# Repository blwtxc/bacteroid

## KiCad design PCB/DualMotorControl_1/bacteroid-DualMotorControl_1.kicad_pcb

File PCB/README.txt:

PCB design: 
KiCAD
http://www.kicad-pcb.org/display/KICAD/KiCad+EDA+Software+Suite

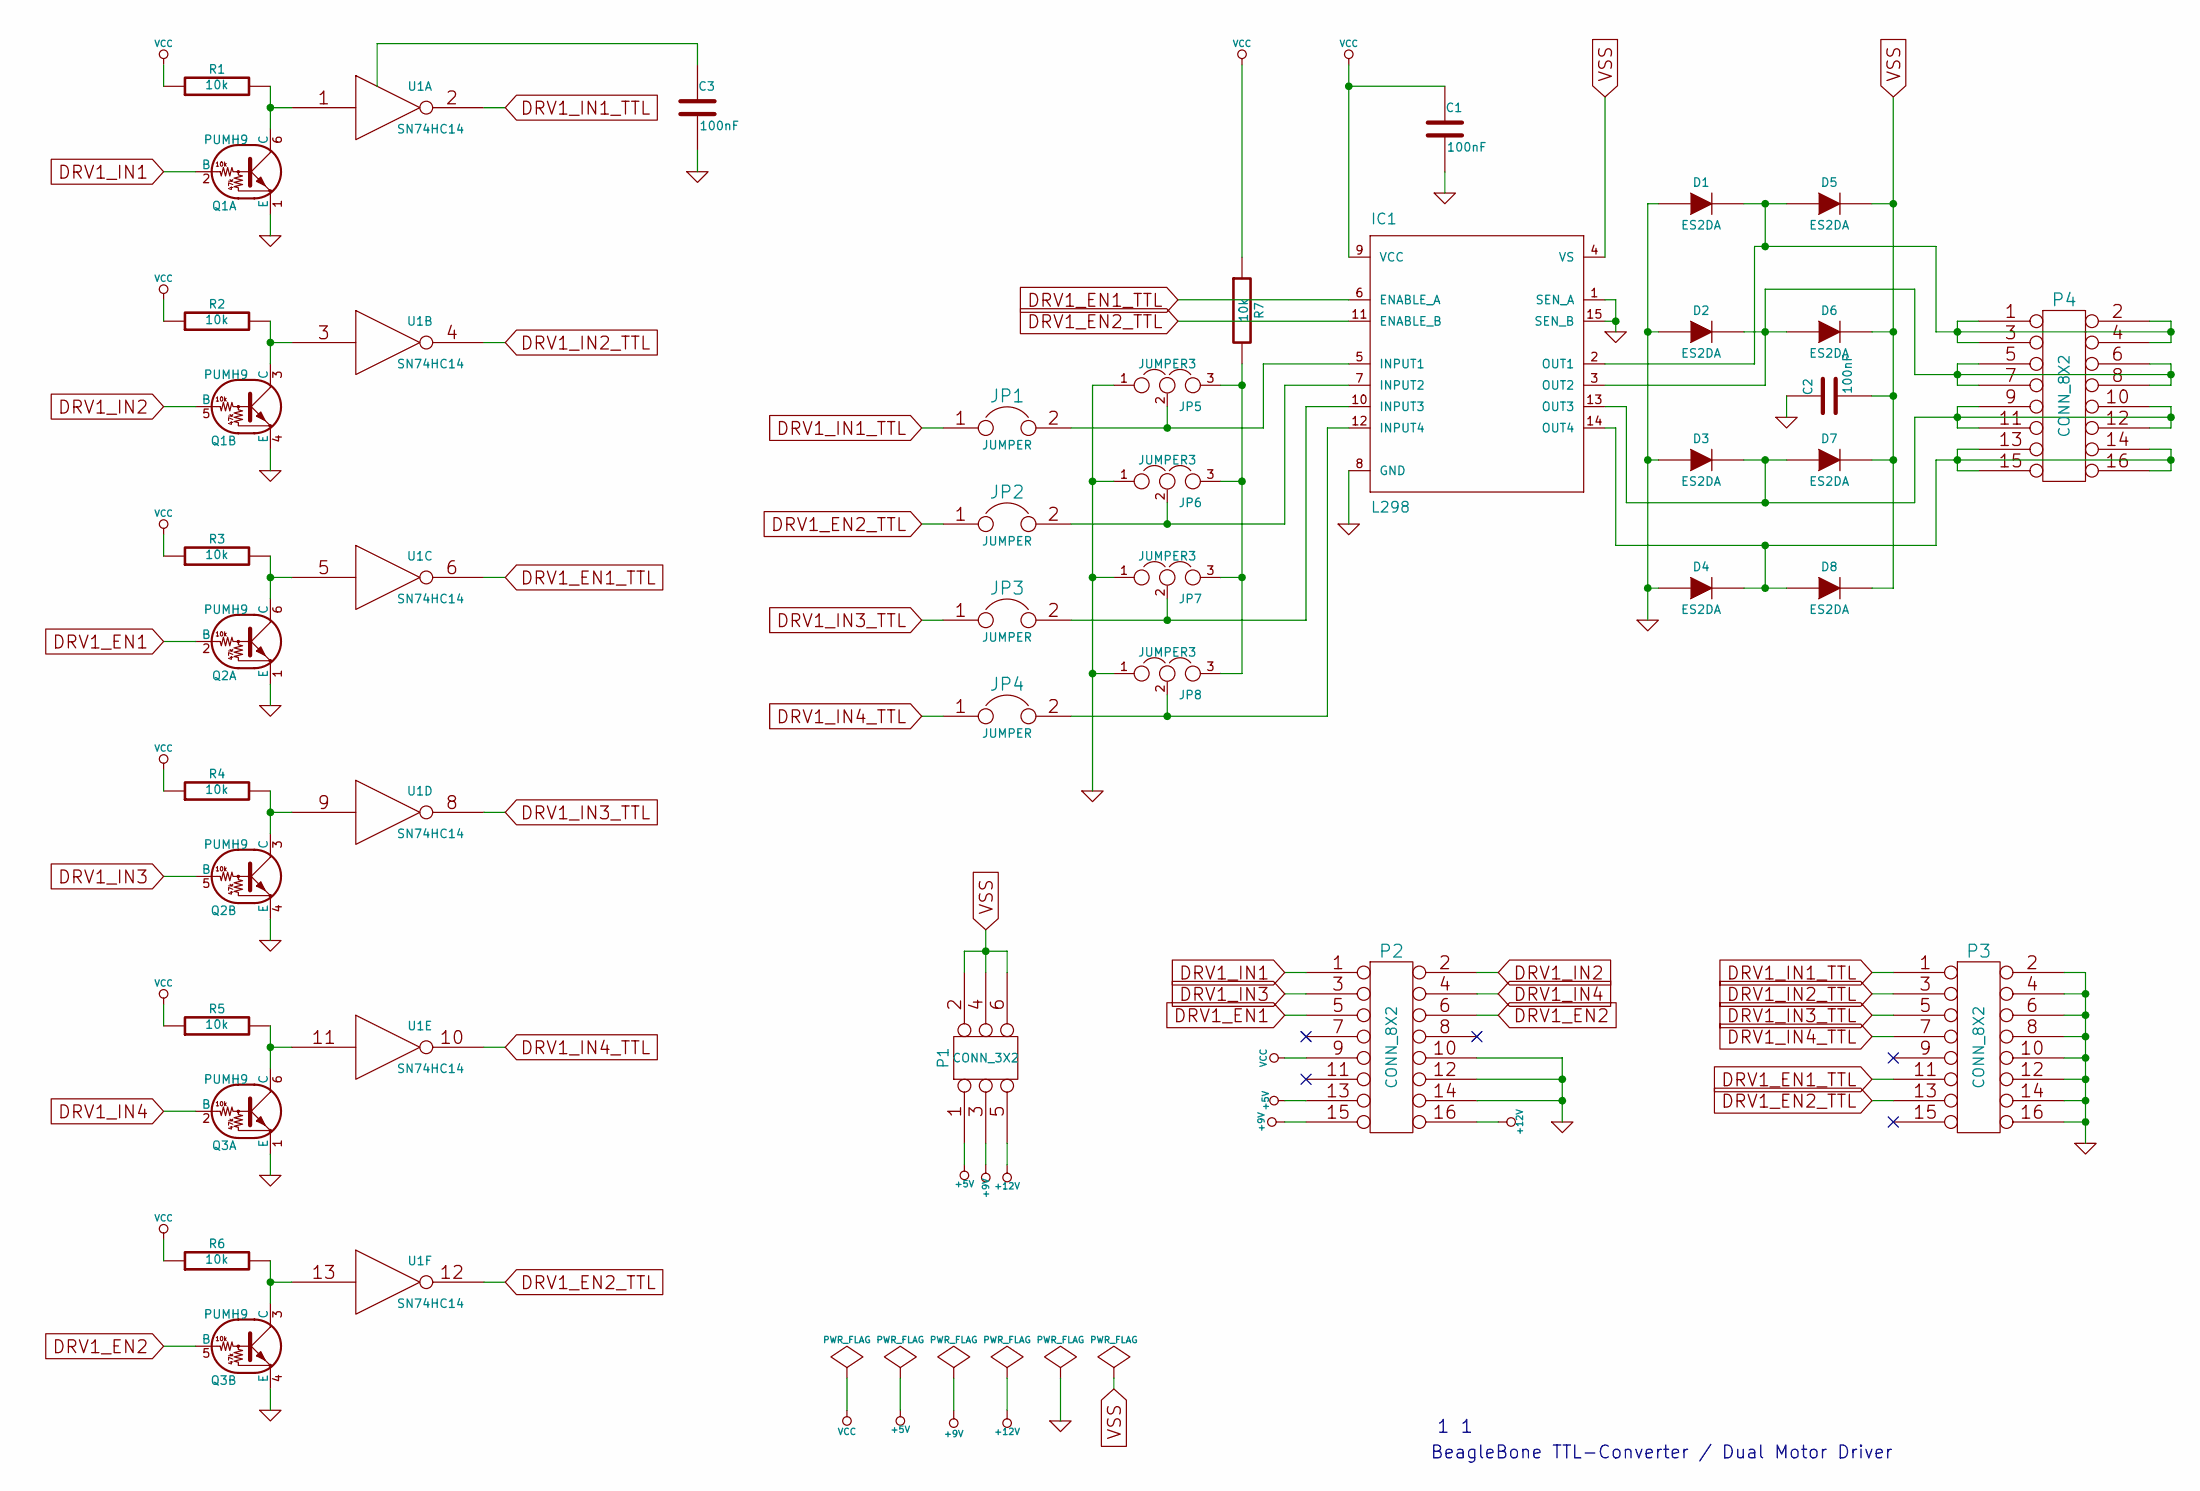
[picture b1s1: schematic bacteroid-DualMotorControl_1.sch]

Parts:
C1, C2, C3: 100nF
D1, D2, D3, D4, D5, D6, D7, D8: ES2DA
IC1: L298; st-microelectronics-MULTIWATT-15
JP1, JP2, JP3, JP4: JUMPER
JP5, JP6, JP7, JP8: JUMPER3
P1: CONN_3X2
P2, P3, P4: CONN_8X2
Q1, Q2, Q3: PUMH9
R1, R2, R3, R4, R5, R6, R7: 10k
U1: SN74HC14

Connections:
+5V: P1.1, P2.13
+9V: P1.3, P2.15
+12V: P1.5, P2.16
DRV1_EN1: P2.5, Q2.2 (B)
DRV1_EN1_TTL: IC1.6 (ENABLE_A), P3.11, U1.6
DRV1_EN2: P2.6, Q3.5 (B)
DRV1_EN2_TTL: IC1.11 (ENABLE_B), JP2.1, P3.13, U1.12
DRV1_IN1: P2.1, Q1.2 (B)
DRV1_IN1_TTL: JP1.1, P3.1, U1.2
DRV1_IN2: P2.2, Q1.5 (B)
DRV1_IN2_TTL: P3.3, U1.4
DRV1_IN3: P2.3, Q2.5 (B)
DRV1_IN3_TTL: JP3.1, P3.5, U1.8
DRV1_IN4: P2.4, Q3.2 (B)
DRV1_IN4_TTL: JP4.1, P3.7, U1.10
GND: C1.2, C2.1, C3.2, D1.1 (A), D2.1 (A), D3.1 (A), D4.1 (A), IC1.1 (SEN_A), IC1.8 (GND), IC1.15 (SEN_B), JP5.1, JP6.1, JP7.1, JP8.1, P2.10, P2.12, P2.14, P3.2, P3.4, P3.6, P3.8, P3.10, P3.12, P3.14, P3.16, Q1.1 (E), Q1.4 (E), Q2.1 (E), Q2.4 (E), Q3.1 (E), Q3.4 (E), U1.7 (GND)
unnamed: IC1.5 (INPUT1), JP1.2, JP5.2
unnamed: IC1.7 (INPUT2), JP2.2, JP6.2
unnamed: IC1.10 (INPUT3), JP3.2, JP7.2
unnamed: IC1.12 (INPUT4), JP4.2, JP8.2
unnamed: JP5.3, JP6.3, JP7.3, JP8.3, R7.2
unnamed: D3.2 (K), D7.1 (A), IC1.13 (OUT3), P4.9, P4.10, P4.11, P4.12
unnamed: D2.2 (K), D6.1 (A), IC1.3 (OUT2), P4.5, P4.6, P4.7, P4.8
unnamed: Q3.3 (C), R6.2, U1.13
unnamed: D4.2 (K), D8.1 (A), IC1.14 (OUT4), P4.13, P4.14, P4.15, P4.16
unnamed: D1.2 (K), D5.1 (A), IC1.2 (OUT1), P4.1, P4.2, P4.3, P4.4
unnamed: Q3.6 (C), R5.2, U1.11
unnamed: Q1.3 (C), R2.2, U1.3
unnamed: Q2.6 (C), R3.2, U1.5
unnamed: Q2.3 (C), R4.2, U1.9
unnamed: Q1.6 (C), R1.2, U1.1
VSS: C2.2, D5.2 (K), D6.2 (K), D7.2 (K), D8.2 (K), IC1.4 (VS), P1.2, P1.4, P1.6

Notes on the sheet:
BeagleBone TTL-Converter / Dual Motor Driver

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
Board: 2 copper layers, 35 parts (0 on the bottom side), 33 nets, no tracks yet.

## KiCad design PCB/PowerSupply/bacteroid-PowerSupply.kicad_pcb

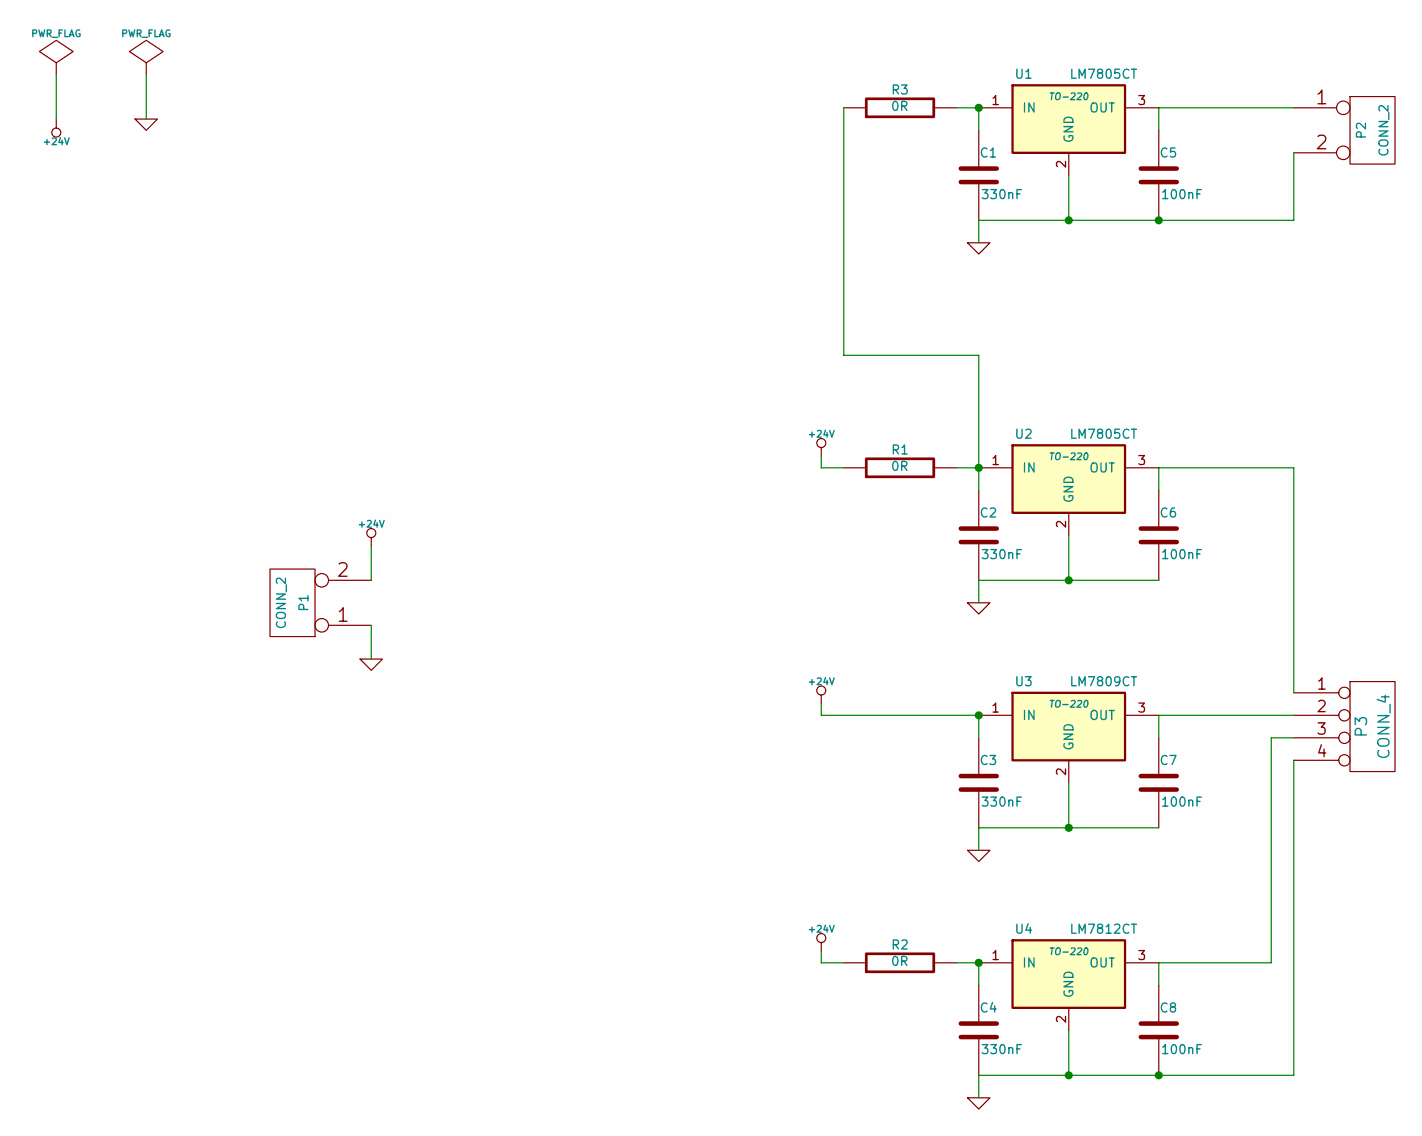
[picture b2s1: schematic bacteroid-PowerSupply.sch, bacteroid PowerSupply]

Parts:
C1, C2, C3, C4: 330nF
C5, C6, C7, C8: 100nF
P1, P2: CONN_2
P3: CONN_4
R1, R2, R3: 0R
U1, U2: LM7805CT; TO-220
U3: LM7809CT; TO-220
U4: LM7812CT; TO-220

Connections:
+24V: C3.1, P1.2 (PM), R1.1, R2.1, U3.1 (IN)
GND: C1.2, C2.2, C3.2, C4.2, C5.2, C6.2, C7.2, C8.2, P1.1, P2.2 (PM), P3.4, U1.2 (GND), U2.2 (GND), U3.2 (GND), U4.2 (GND)
unnamed: C4.1, R2.2, U4.1 (IN)
unnamed: C7.1, P3.2, U3.3 (OUT)
unnamed: C2.1, R1.2, R3.1, U2.1 (IN)
unnamed: C5.1, P2.1, U1.3 (OUT)
unnamed: C1.1, R3.2, U1.1 (IN)
unnamed: C8.1, P3.3, U4.3 (OUT)
unnamed: C6.1, P3.1, U2.3 (OUT)

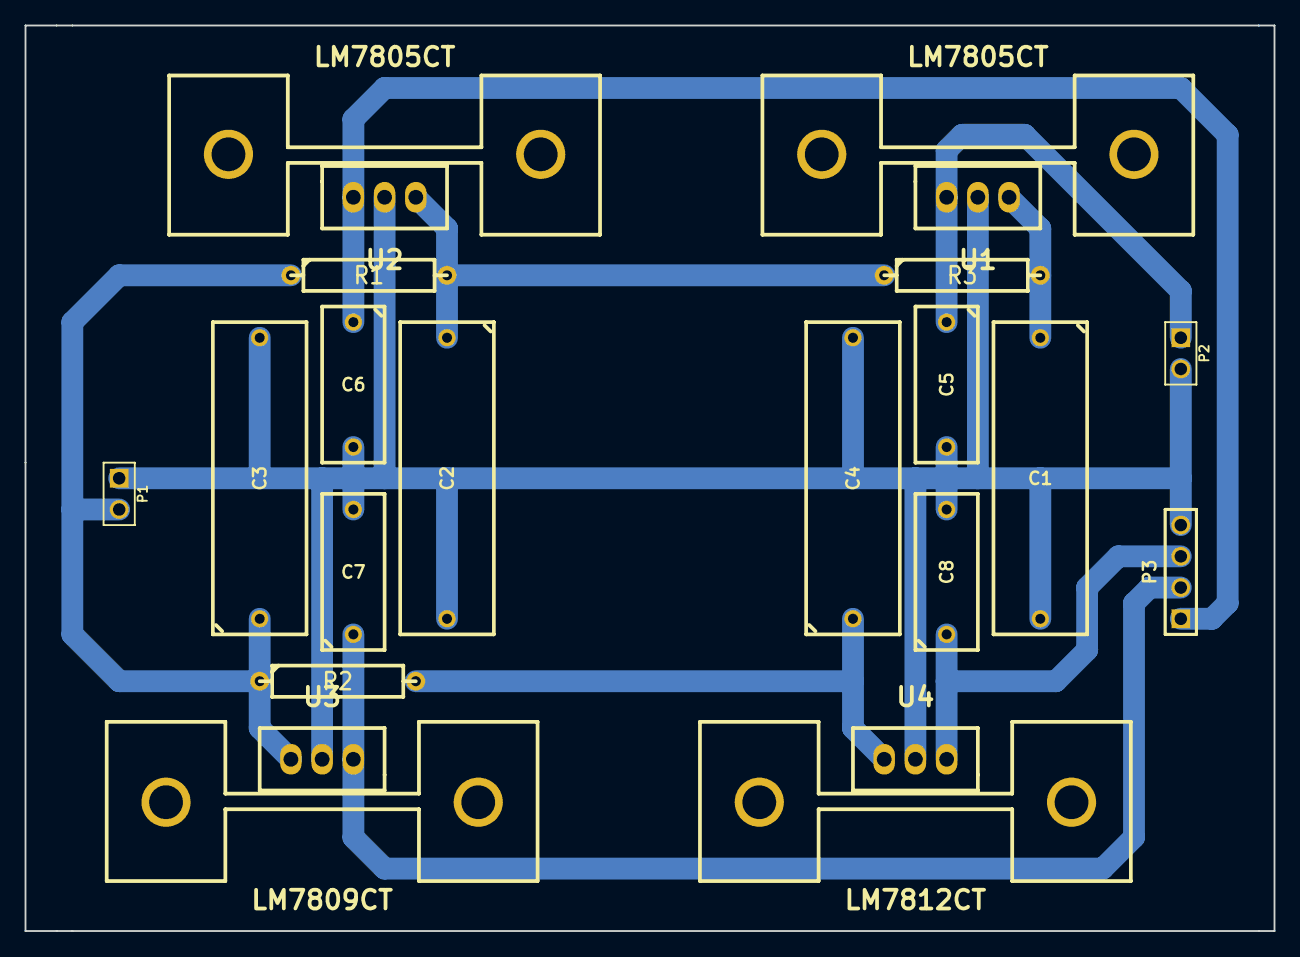
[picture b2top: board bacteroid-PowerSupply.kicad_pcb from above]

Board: 2 copper layers, 101.6 x 73.7 mm, 18 parts (0 on the bottom side), 9 nets.

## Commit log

2013-09-12 init commit
2013-09-12 Add READMEs for smisioto components
2013-10-02 PCB Updates
2013-10-10 PCB update
